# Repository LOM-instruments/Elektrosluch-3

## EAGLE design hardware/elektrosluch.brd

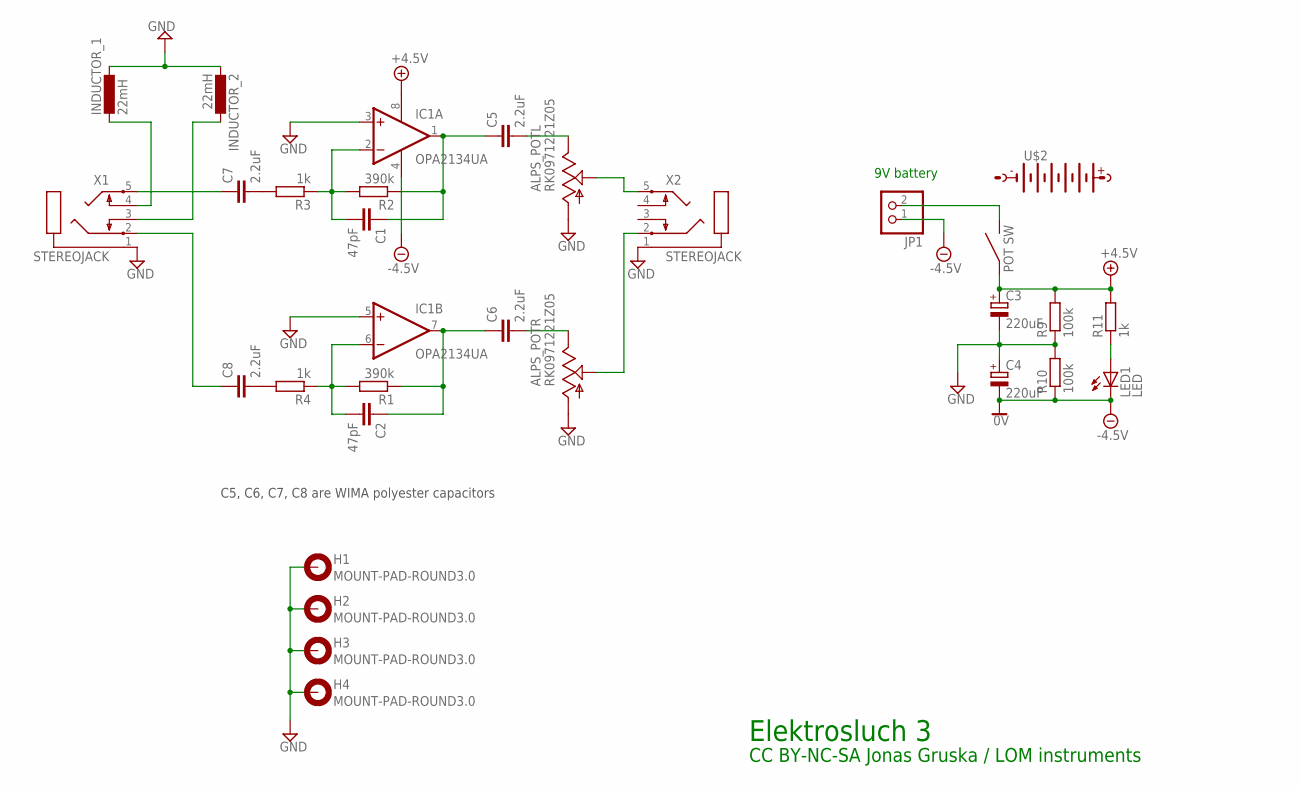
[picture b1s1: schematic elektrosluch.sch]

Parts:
ALPS_POT: RK0971221Z05; ALPS_RK0971221Z0X
C1, C2: 47pF; C0805
C3, C4: 220uF; PANASONIC_D
C5, C6, C7, C8: 2.2uF; WIMA10UF
H1, H2, H3, H4: MOUNT-PAD-ROUND3.0; 3,0-PAD
IC1: OPA2134UA; SO08
INDUCTOR_1, INDUCTOR_2: 22mH; COIL
JP1: PINHD-1X2; 1X02
LED1: LED; LED3MM
R1, R2: 390k; R0805
R3, R4, R11: 1k; R0805
R9, R10: 100k; R0805
U$2: BATT
X1, X2: STEREOJACK; STX3100

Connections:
+5V: ALPS_POT.S1, C3.+, IC1.8 (V+), R9.2, R11.2
-5V: C4.-, IC1.4 (V-), JP1.1, LED1.K (C), R10.1
GND: ALPS_POT.G1 (1), ALPS_POT.G2 (1), C3.-, C4.+, H1.B3,0, H2.B3,0, H3.B3,0, H4.B3,0, IC1.3 (+IN), IC1.5 (+IN), INDUCTOR_1.P$1 (1), INDUCTOR_2.P$2 (2), R9.1, R10.2, X1.1, X2.1
unnamed: C1.2, IC1.2 (-IN), R2.2, R3.1
unnamed: C1.1, C5.P$1 (1), IC1.1 (OUT), R2.1
unnamed: ALPS_POT.I1 (3), C5.P$2 (2)
unnamed: C2.2, IC1.6 (-IN), R1.2, R4.1
unnamed: C2.1, C6.P$1 (1), IC1.7 (OUT), R1.1
unnamed: ALPS_POT.I2 (3), C6.P$2 (2)
unnamed: ALPS_POT.O1 (2), X2.5
unnamed: C7.P$1 (1), X1.5
unnamed: ALPS_POT.O2 (2), X2.2
unnamed: C8.P$1 (1), X1.2
unnamed: C7.P$2 (2), R3.2
unnamed: INDUCTOR_1.P$2 (2), X1.4
unnamed: INDUCTOR_2.P$1 (1), X1.3
unnamed: LED1.A, R11.1
unnamed: C8.P$2 (2), R4.2
unnamed: ALPS_POT.S2, JP1.2

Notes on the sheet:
9V battery
Elektrosluch 3
CC BY-NC-SA Jonas Gruska / LOM instruments
C5, C6, C7, C8 are WIMA polyester capacitors

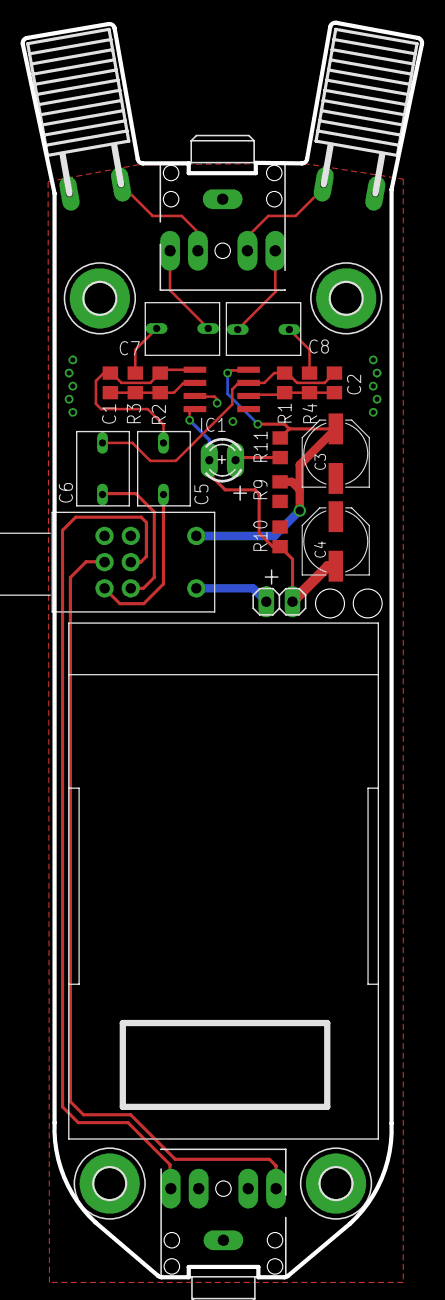
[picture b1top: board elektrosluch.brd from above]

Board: 2 copper layers, 38.7 x 121.6 mm, 30 parts (0 on the bottom side), 19 nets.

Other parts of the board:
U$3: ELEKTROSLUCH3
U$4: LOM_BACK

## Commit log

2015-08-26 first
